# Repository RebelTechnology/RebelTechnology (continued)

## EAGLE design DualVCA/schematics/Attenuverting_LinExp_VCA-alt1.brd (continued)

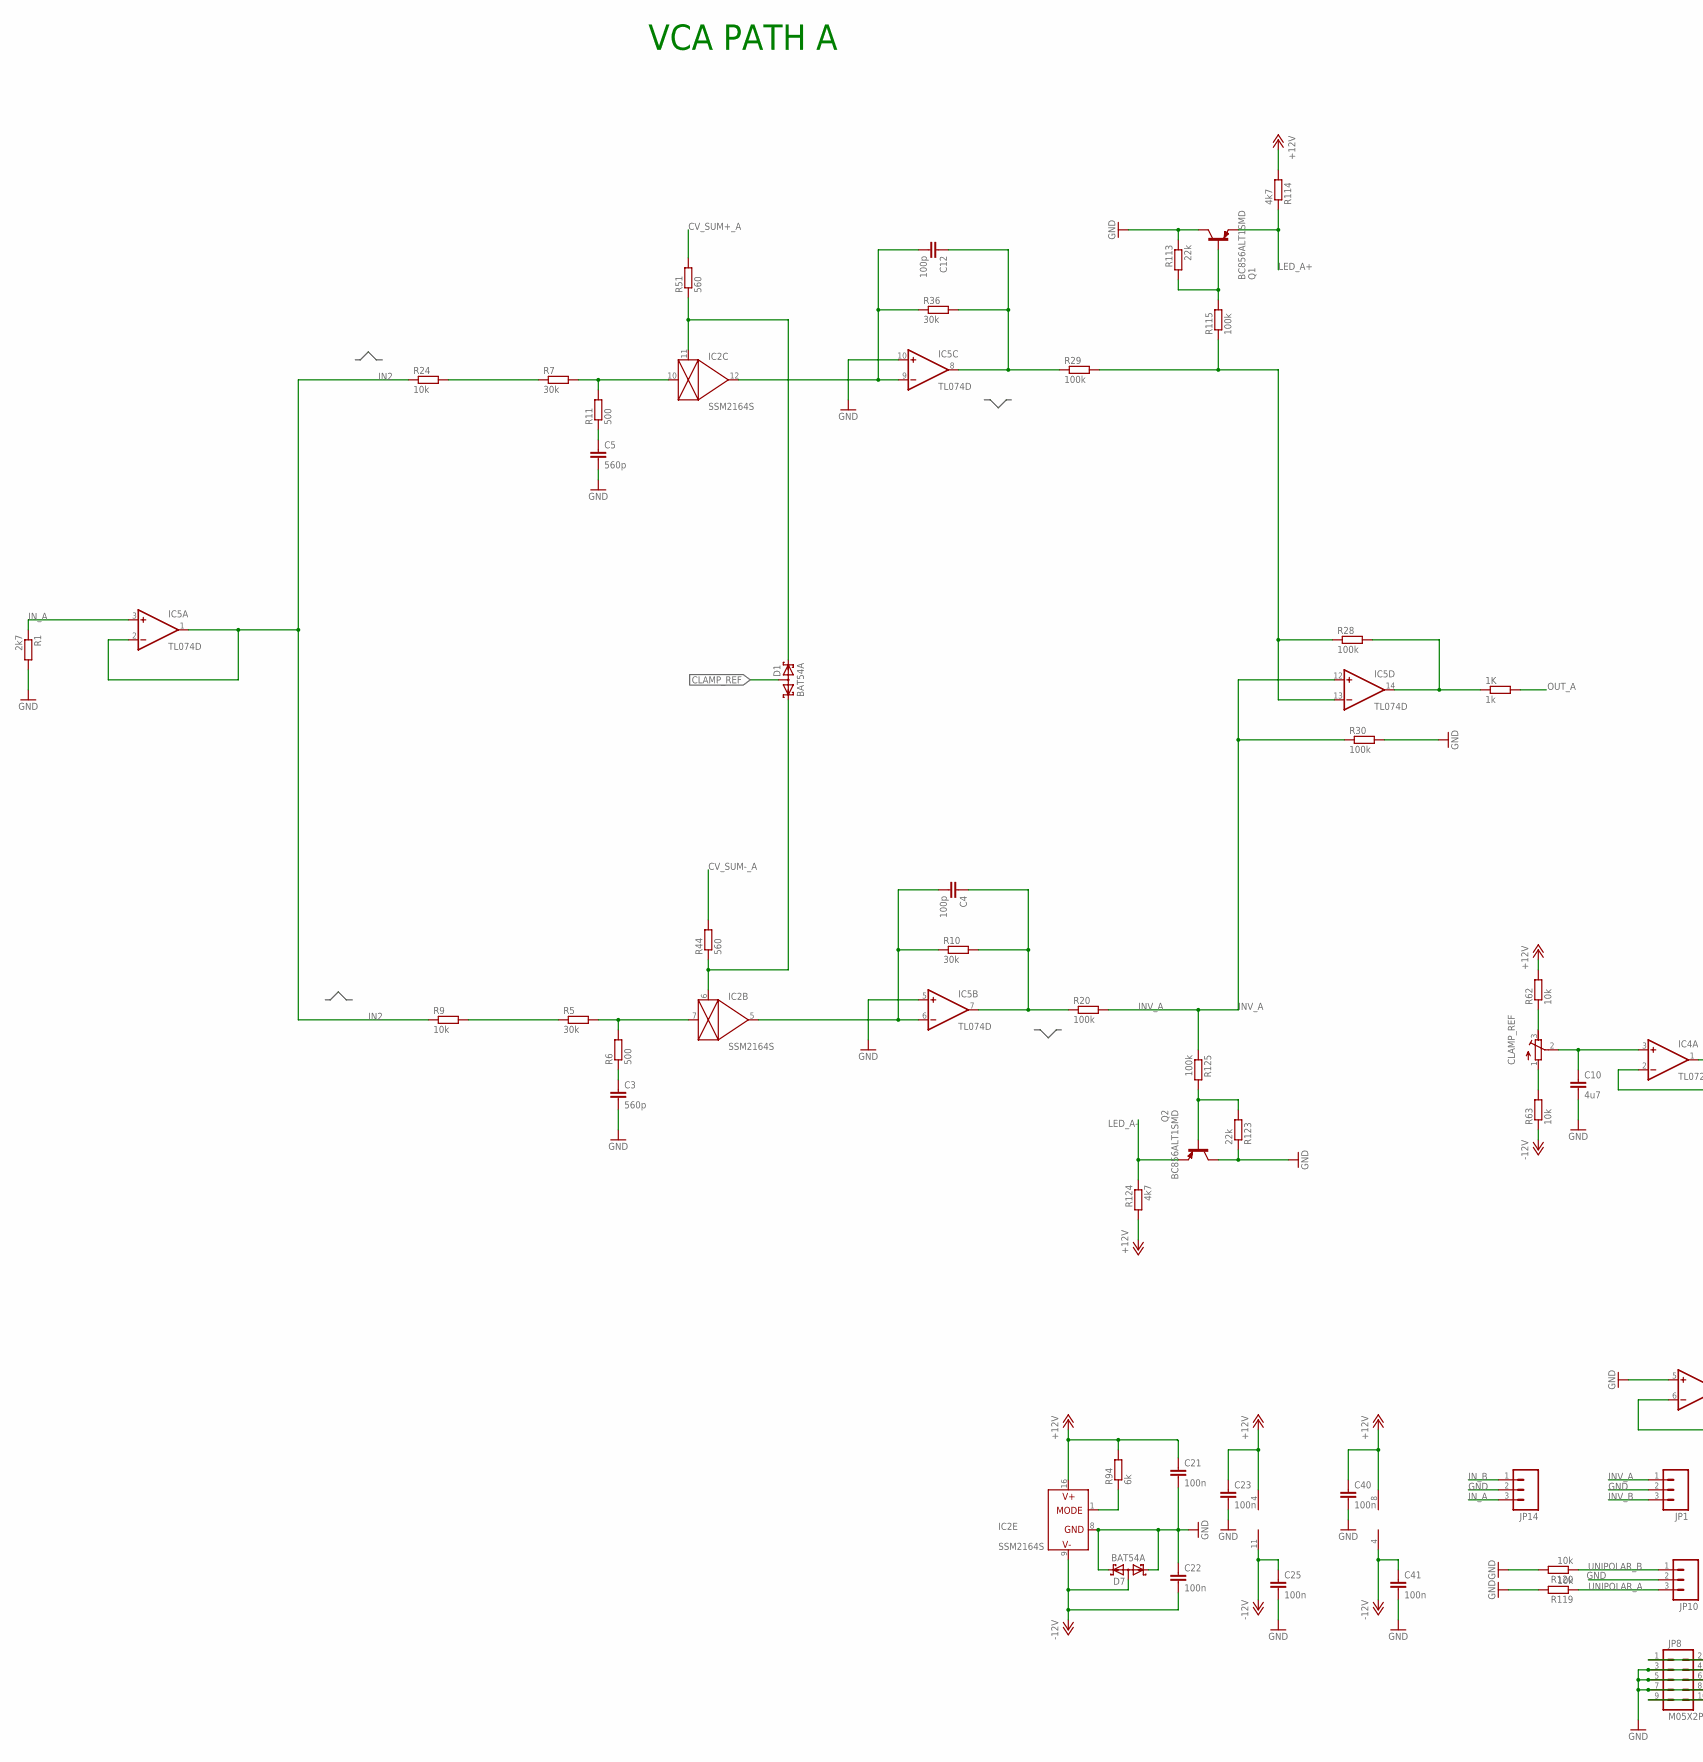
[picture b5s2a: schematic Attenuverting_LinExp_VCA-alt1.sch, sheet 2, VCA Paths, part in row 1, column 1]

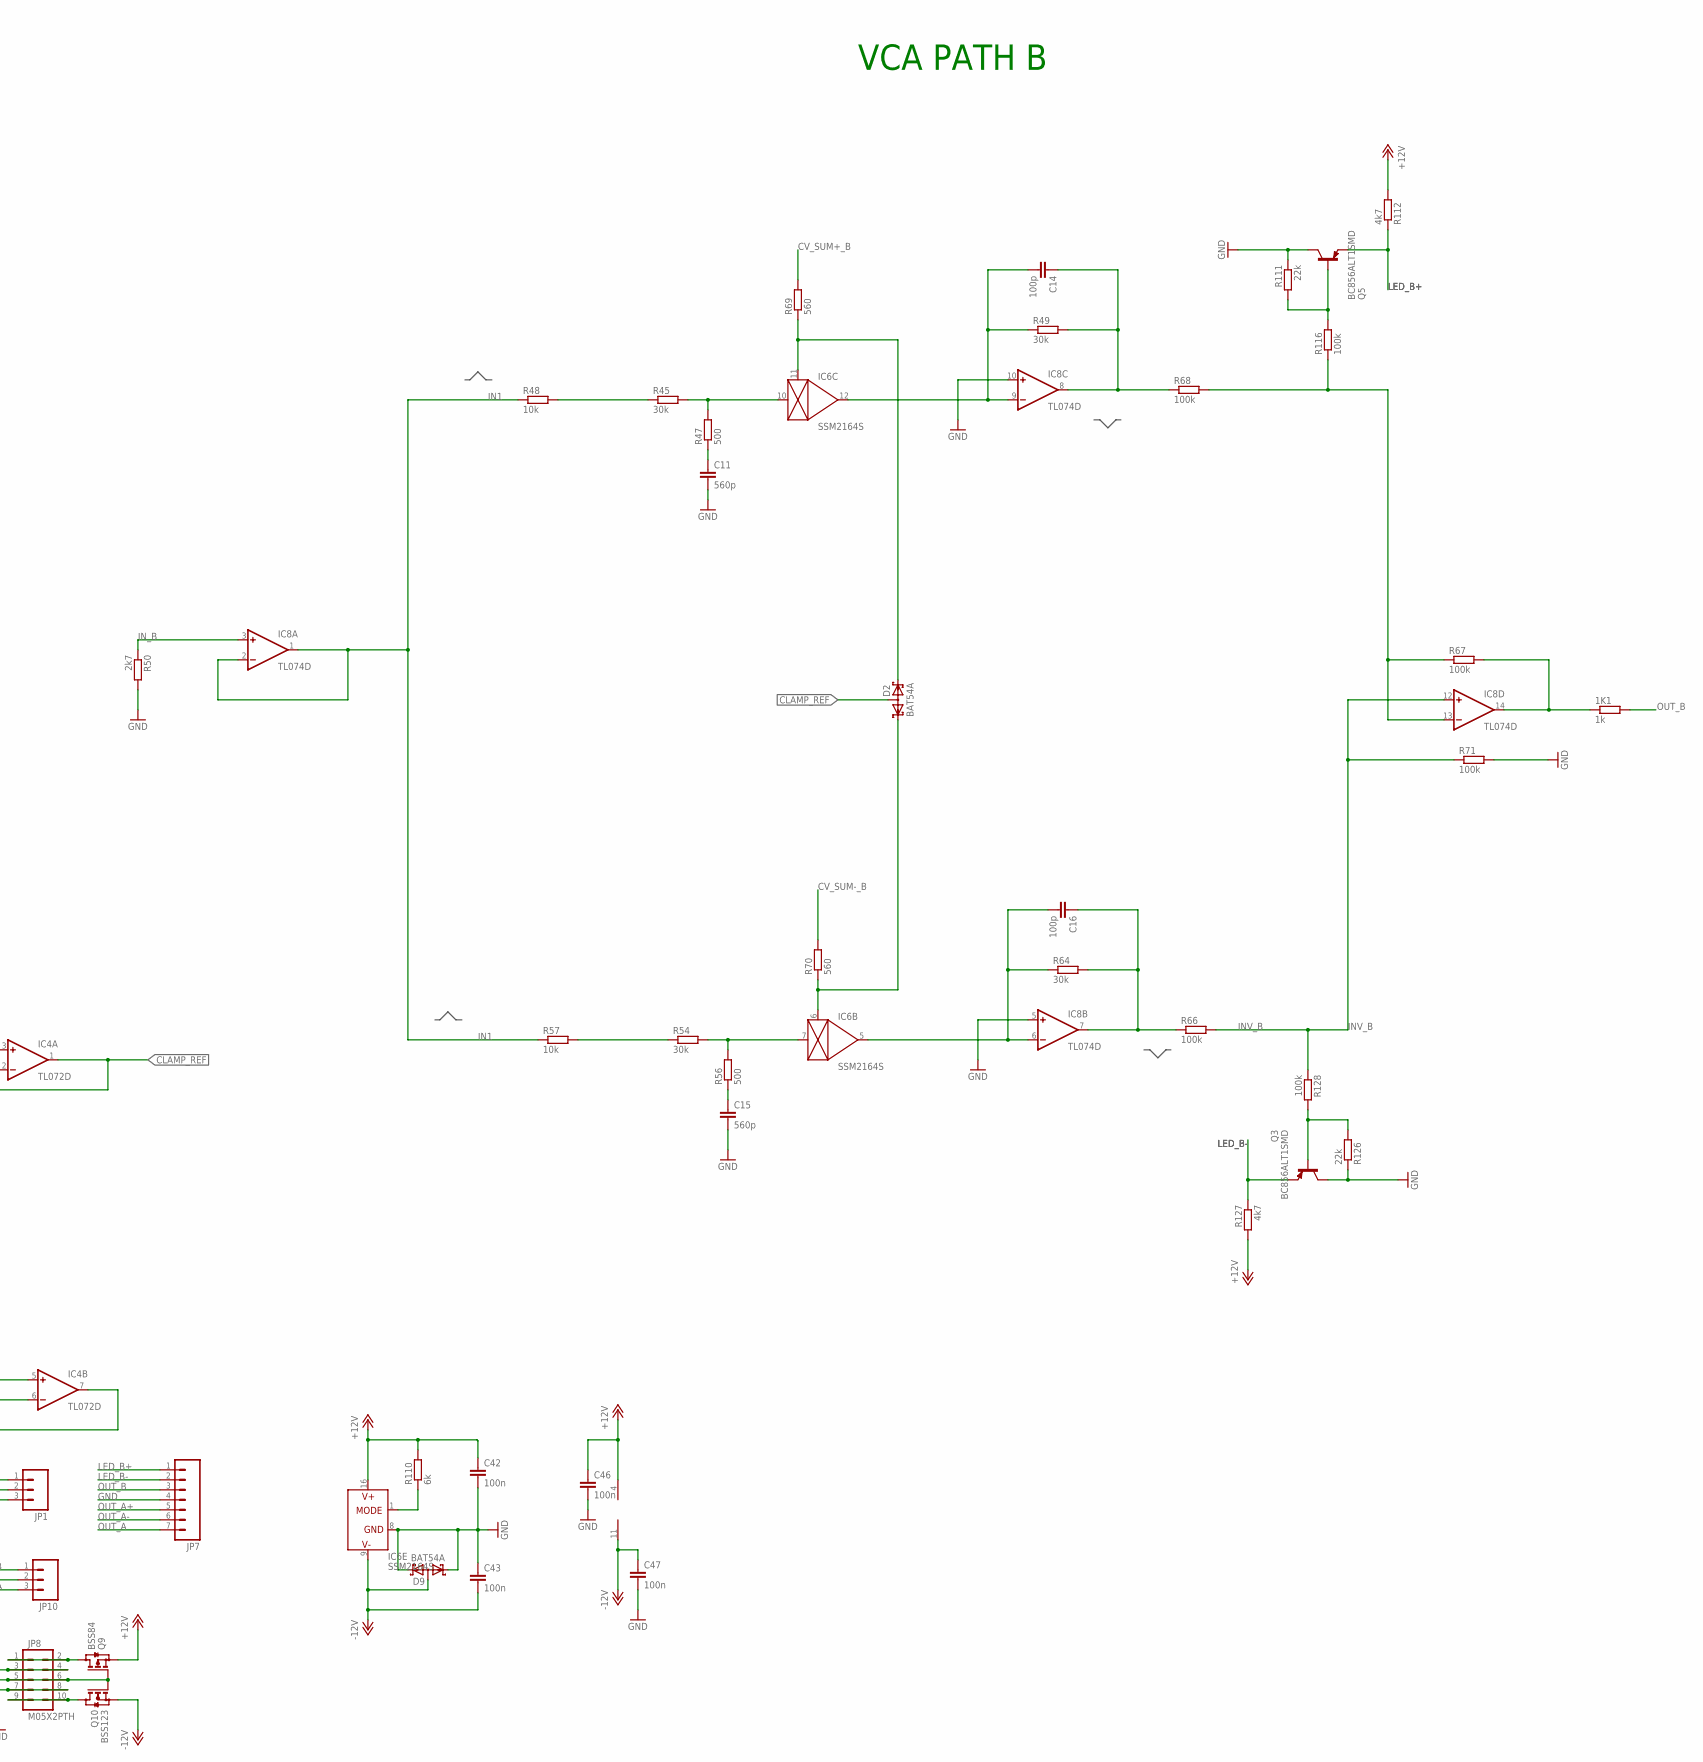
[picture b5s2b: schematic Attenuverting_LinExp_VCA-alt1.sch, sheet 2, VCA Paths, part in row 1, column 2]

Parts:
1K, 1K1: 1k; 0603; MPN MC0063W06031160K
C3, C5, C11, C15: 560p; C0603K
C4, C12, C14, C16: 100p; C0603K
C10: 4u7; C0603K
C21, C22, C23, C25, C40, C41, C42, C43, C46, C47: 100n; C0603K
CLAMP_REF: R-TRIMM64W; RTRIM64W
D1, D2, D7, D9: BAT54A; SOT23
IC2, IC6: SSM2164S; SOIC16N
IC4: TL072D; SO08
IC5, IC8: TL074D; SO14
JP1, JP10, JP14: M03PTH; 1X03
JP7: M07; 1X07
JP8: M05X2PTH; AVR_ICSP
Q1, Q2, Q3, Q5: BC856ALT1SMD; SOT23-BEC
Q9: BSS84; SOT23
Q10: BSS123; SOT23
R1, R50: 2k7; 0603
R5, R7, R10, R36, R45, R49, R54, R64: 30k; 0603
R6, R11, R47, R56: 500; 0603
R9, R24, R48, R57, R62, R63, R119, R120: 10k; 0603
R20, R28, R29, R30, R66, R67, R68, R71, R115, R116, R125, R128: 100k; 0603
R44, R51, R69, R70: 560; 0603
R94, R110: 6k; 0603
R111, R113, R123, R126: 22k; 0603
R112, R114, R124, R127: 4k7; 0603

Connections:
+12V: C21.1, C23.1, C40.1, C42.1, C46.1, IC2.16 (V+), IC4.8 (V+), IC5.4 (V+), IC6.16 (V+), IC8.4 (V+), Q9.2 (S), R62.2, R94.2, R110.2, R112.2, R114.2, R124.2, R127.2; also elsewhere on the board
-12V: C22.2, C25.1, C41.1, C43.2, C47.1, D7.3 (AA), D9.3 (AA), IC2.9 (V-), IC4.4 (V-), IC5.11 (V-), IC6.9 (V-), IC8.11 (V-), Q10.2 (S), R63.1; also elsewhere on the board
CLAMP_REF: D1.3 (AA), D2.3 (AA), IC4.1 (OUT), IC4.2 (-IN)
CV_SUM+_A: R51.2; also elsewhere on the board
CV_SUM+_B: R69.2; also elsewhere on the board
CV_SUM-_A: R44.2; also elsewhere on the board
CV_SUM-_B: R70.2; also elsewhere on the board
GND: C3.2, C5.2, C10.2, C11.2, C15.2, C21.2, C22.1, C23.2, C25.2, C40.2, C41.2, C42.2, C43.1, C46.2, C47.2, D7.1 (K1), D7.2 (K2), D9.1 (K1), D9.2 (K2), IC2.8 (GND), IC4.5 (+IN), IC5.5 (+IN), IC5.10 (+IN), IC6.8 (GND), IC8.5 (+IN), IC8.10 (+IN), JP1.2, JP7.4, JP8.3, JP8.4, JP8.5, JP8.6, JP8.7, JP8.8, JP10.2, JP14.2, Q1.C, Q2.C, Q3.C, Q5.C, Q9.1 (G), Q10.1 (G), R1.2, R30.2, R50.2, R71.2, R111.1, R113.1, R119.2, R120.2, R123.1, R126.1; also elsewhere on the board
IC2B_1: D2.1 (K1), IC6.6 (CTRL), R70.1
IC2B_6: D1.1 (K1), IC2.6 (CTRL), R44.1
IC2C_1: D2.2 (K2), IC6.11 (CTRL), R69.1
IC2C_11: D1.2 (K2), IC2.11 (CTRL), R51.1
IN1: IC8.1 (OUT), IC8.2 (-IN), R48.1, R57.1
IN2: IC5.1 (OUT), IC5.2 (-IN), R9.1, R24.1
INV_A: IC5.12 (+IN), JP1.1, R20.2, R30.1, R125.1; also elsewhere on the board
INV_B: IC8.12 (+IN), JP1.3, R66.2, R71.1, R128.1; also elsewhere on the board
IN_A: IC5.3 (+IN), JP14.3, R1.1; also elsewhere on the board
IN_B: IC8.3 (+IN), JP14.1, R50.1; also elsewhere on the board
LED_A+: Q1.E, R114.1; also elsewhere on the board
LED_A-: Q2.E, R124.1; also elsewhere on the board
LED_B+: JP7.1, Q5.E, R112.1; also elsewhere on the board
LED_B-: JP7.2, Q3.E, R127.1; also elsewhere on the board
unnamed: JP8.9, JP8.10, Q10.3 (D)
unnamed: C3.1, R6.1
unnamed: JP8.1, JP8.2, Q9.3 (D)
unnamed: Q2.B, R123.2, R125.2
unnamed: IC5.13 (-IN), R28.1, R29.2, R115.1
unnamed: IC2.7 (IN), R5.2, R6.2
unnamed: R5.1, R9.2
unnamed: C5.1, R11.1
unnamed: C4.2, IC2.5 (OUT), IC5.6 (-IN), R10.1
unnamed: C4.1, IC5.7 (OUT), R10.2, R20.1
unnamed: IC2.10 (IN), R7.2, R11.2
unnamed: 1K.1, IC5.14 (OUT), R28.2
unnamed: C11.1, R47.1
unnamed: R7.1, R24.2
unnamed: Q3.B, R126.2, R128.2
unnamed: IC6.10 (IN), R45.2, R47.2
unnamed: CLAMP_REF.3 (E), R62.1
unnamed: Q5.B, R111.2, R116.2
unnamed: R45.1, R48.2
unnamed: C14.2, IC6.12 (OUT), IC8.9 (-IN), R49.1
unnamed: C14.1, IC8.8 (OUT), R49.2, R68.1
unnamed: C15.1, R56.1
unnamed: IC6.7 (IN), R54.2, R56.2
unnamed: C12.2, IC2.12 (OUT), IC5.9 (-IN), R36.1
unnamed: R54.1, R57.2
unnamed: C12.1, IC5.8 (OUT), R29.1, R36.2
unnamed: C16.2, IC6.5 (OUT), IC8.6 (-IN), R64.1
unnamed: CLAMP_REF.1 (A), R63.2
unnamed: C10.1, CLAMP_REF.2 (S), IC4.3 (+IN)
unnamed: C16.1, IC8.7 (OUT), R64.2, R66.1
unnamed: IC8.13 (-IN), R67.1, R68.2, R116.1
unnamed: 1K1.1, IC8.14 (OUT), R67.2
unnamed: IC2.1 (MODE), R94.1
unnamed: IC4.6 (-IN), IC4.7 (OUT)
unnamed: Q1.B, R113.2, R115.2
unnamed: IC6.1 (MODE), R110.1
OUT_A: 1K.2, JP7.7; also elsewhere on the board
OUT_A+: JP7.5
OUT_A-: JP7.6
OUT_B: 1K1.2, JP7.3; also elsewhere on the board
UNIPOLAR_A: JP10.3, R119.1; also elsewhere on the board
UNIPOLAR_B: JP10.1, R120.1; also elsewhere on the board

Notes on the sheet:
VCA PATH A
VCA PATH B

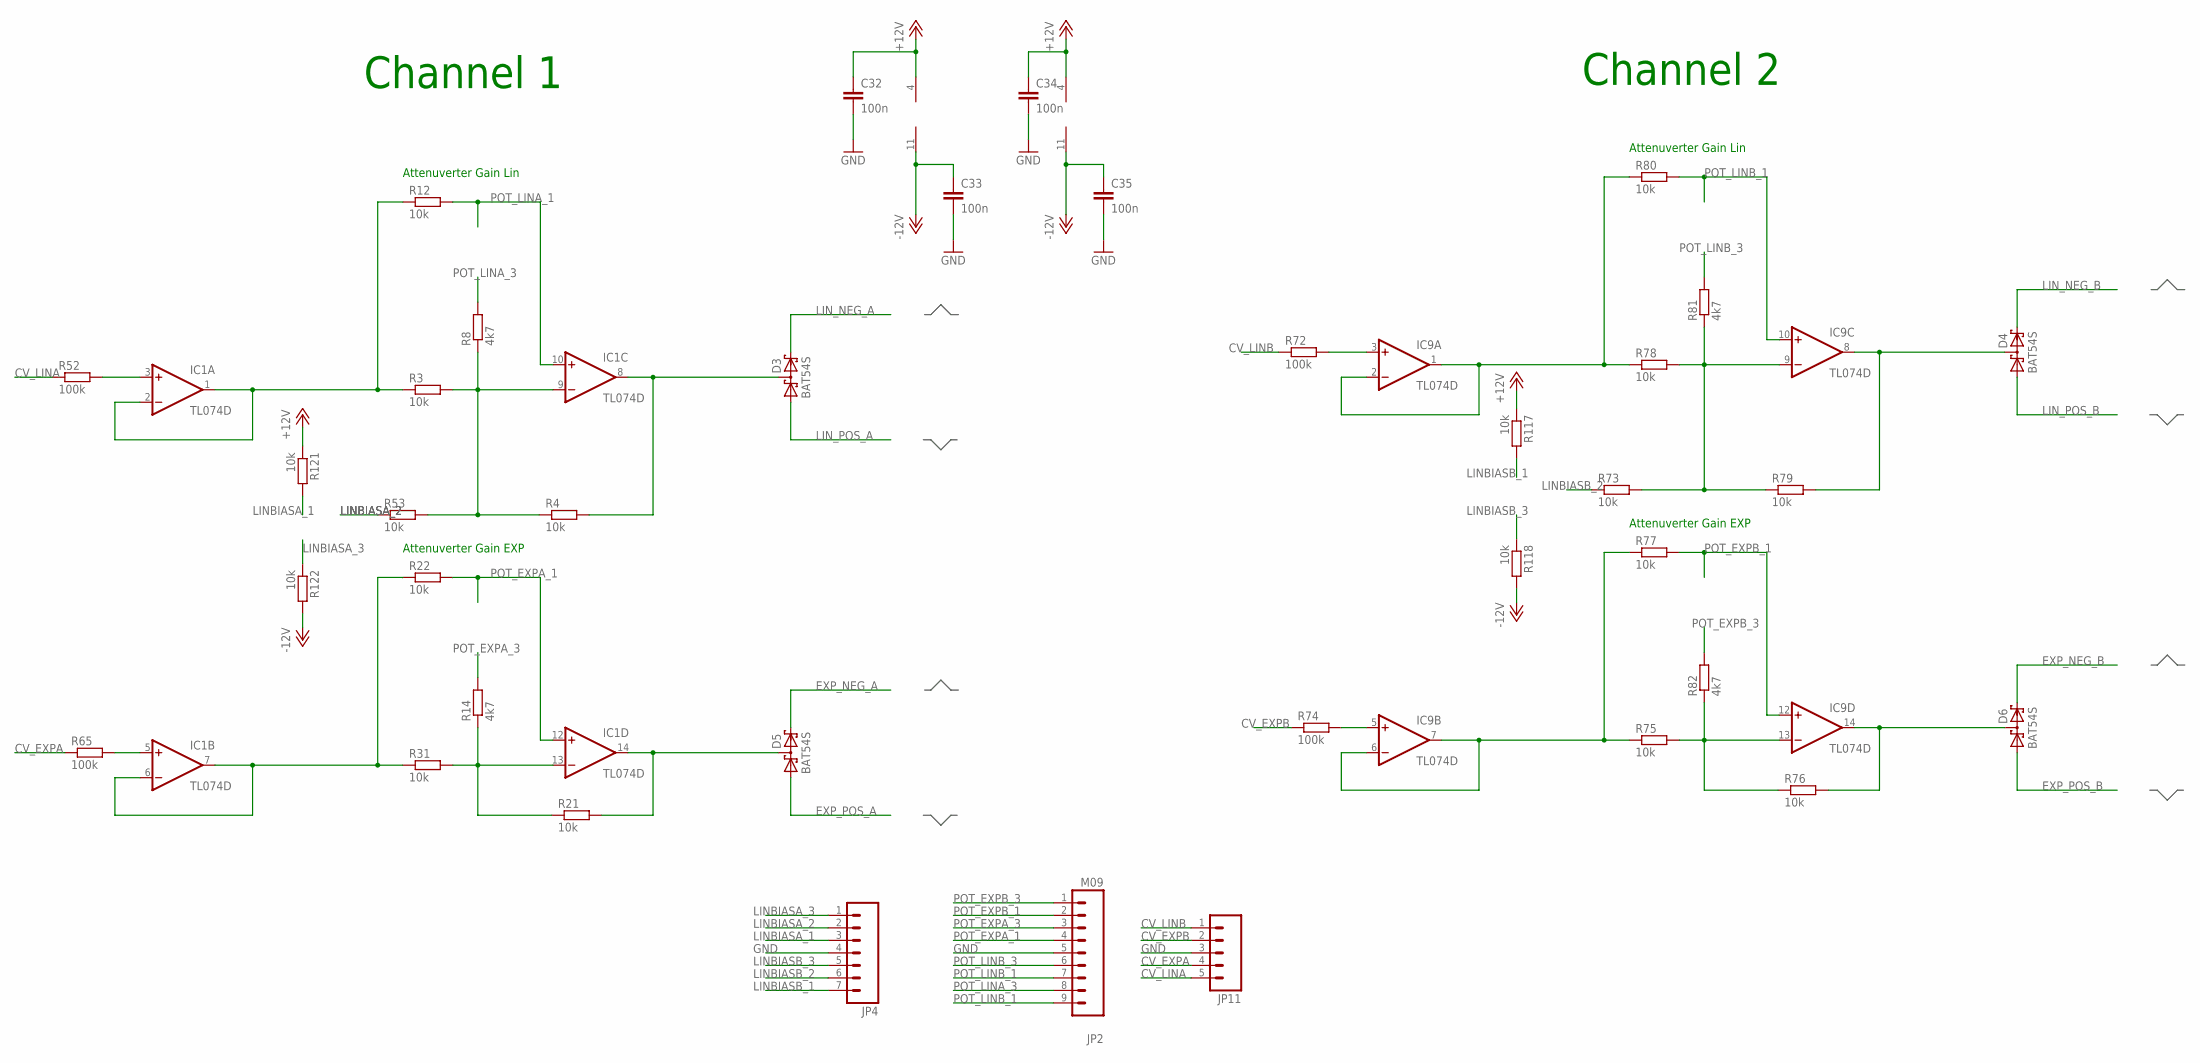
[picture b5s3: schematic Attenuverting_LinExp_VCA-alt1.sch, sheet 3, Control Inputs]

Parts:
C32, C33, C34, C35: 100n; C0603K
D3, D4, D5, D6: BAT54S; SOT23
IC1, IC9: TL074D; SO14
JP2: M09; 1X09
JP4: M07; 1X07
JP11: M05PTH; 1X05
R3, R4, R12, R21, R22, R31, R53, R73, R75, R76, R77, R78, R79, R80, R117, R118, R121, R122: 10k; 0603
R8, R14, R81, R82: 4k7; 0603
R52, R65, R72, R74: 100k; 0603

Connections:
+12V: C32.1, C34.1, IC1.4 (V+), IC9.4 (V+), R117.1, R121.1; also elsewhere on the board
-12V: C33.1, C35.1, IC1.11 (V-), IC9.11 (V-), R118.2, R122.2; also elsewhere on the board
CV_1+: IC1.6 (-IN), IC1.7 (OUT), R22.1, R31.1
CV_1+1: IC9.6 (-IN), IC9.7 (OUT), R75.1, R77.1
CV_1-: IC1.1 (OUT), IC1.2 (-IN), R3.1, R12.1
CV_1-1: IC9.1 (OUT), IC9.2 (-IN), R78.1, R80.1
CV_EXPA: JP11.4, R65.1; also elsewhere on the board
CV_EXPB: JP11.2, R74.1; also elsewhere on the board
CV_LINA: JP11.5, R52.1; also elsewhere on the board
CV_LINB: JP11.1, R72.1; also elsewhere on the board
EXP_NEG_A: D5.2 (C2); also elsewhere on the board
EXP_NEG_B: D6.2 (C2); also elsewhere on the board
EXP_POS_A: D5.1 (A1); also elsewhere on the board
EXP_POS_B: D6.1 (A1); also elsewhere on the board
GND: C32.2, C33.2, C34.2, C35.2, JP2.5, JP4.4, JP11.3; also elsewhere on the board
LINBIASA_1: JP4.3, R121.2; also elsewhere on the board
LINBIASA_2: JP4.2, R53.1; also elsewhere on the board
LINBIASA_3: JP4.1, R122.1; also elsewhere on the board
LINBIASB_1: JP4.7, R117.2; also elsewhere on the board
LINBIASB_2: JP4.6, R73.1; also elsewhere on the board
LINBIASB_3: JP4.5, R118.1; also elsewhere on the board
LIN_NEG_A: D3.2 (C2); also elsewhere on the board
LIN_NEG_B: D4.2 (C2); also elsewhere on the board
LIN_POS_A: D3.1 (A1); also elsewhere on the board
LIN_POS_B: D4.1 (A1); also elsewhere on the board
unnamed: D3.3 (C1A2), IC1.8 (OUT), R4.2
unnamed: IC1.3 (+IN), R52.2
unnamed: IC1.5 (+IN), R65.2
unnamed: IC1.13 (-IN), R14.1, R21.1, R31.2
unnamed: IC1.9 (-IN), R3.2, R4.1, R8.1, R53.2
unnamed: D6.3 (C1A2), IC9.14 (OUT), R76.2
unnamed: IC9.13 (-IN), R75.2, R76.1, R82.1
unnamed: D4.3 (C1A2), IC9.8 (OUT), R79.2
unnamed: IC9.3 (+IN), R72.2
unnamed: IC9.5 (+IN), R74.2
unnamed: IC9.9 (-IN), R73.2, R78.2, R79.1, R81.1
unnamed: D5.3 (C1A2), IC1.14 (OUT), R21.2
POT_EXPA_1: IC1.12 (+IN), JP2.4, R22.2; also elsewhere on the board
POT_EXPA_3: JP2.3, R14.2; also elsewhere on the board
POT_EXPB_1: IC9.12 (+IN), JP2.2, R77.2; also elsewhere on the board
POT_EXPB_3: JP2.1, R82.2; also elsewhere on the board
POT_LINA_1: IC1.10 (+IN), R12.2; also elsewhere on the board
POT_LINA_3: JP2.8, R8.2; also elsewhere on the board
POT_LINB_1: IC9.10 (+IN), JP2.7, JP2.9, R80.2; also elsewhere on the board
POT_LINB_3: JP2.6, R81.2; also elsewhere on the board

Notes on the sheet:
Attenuverter Gain Lin
Attenuverter Gain EXP
Channel 1
Channel 2

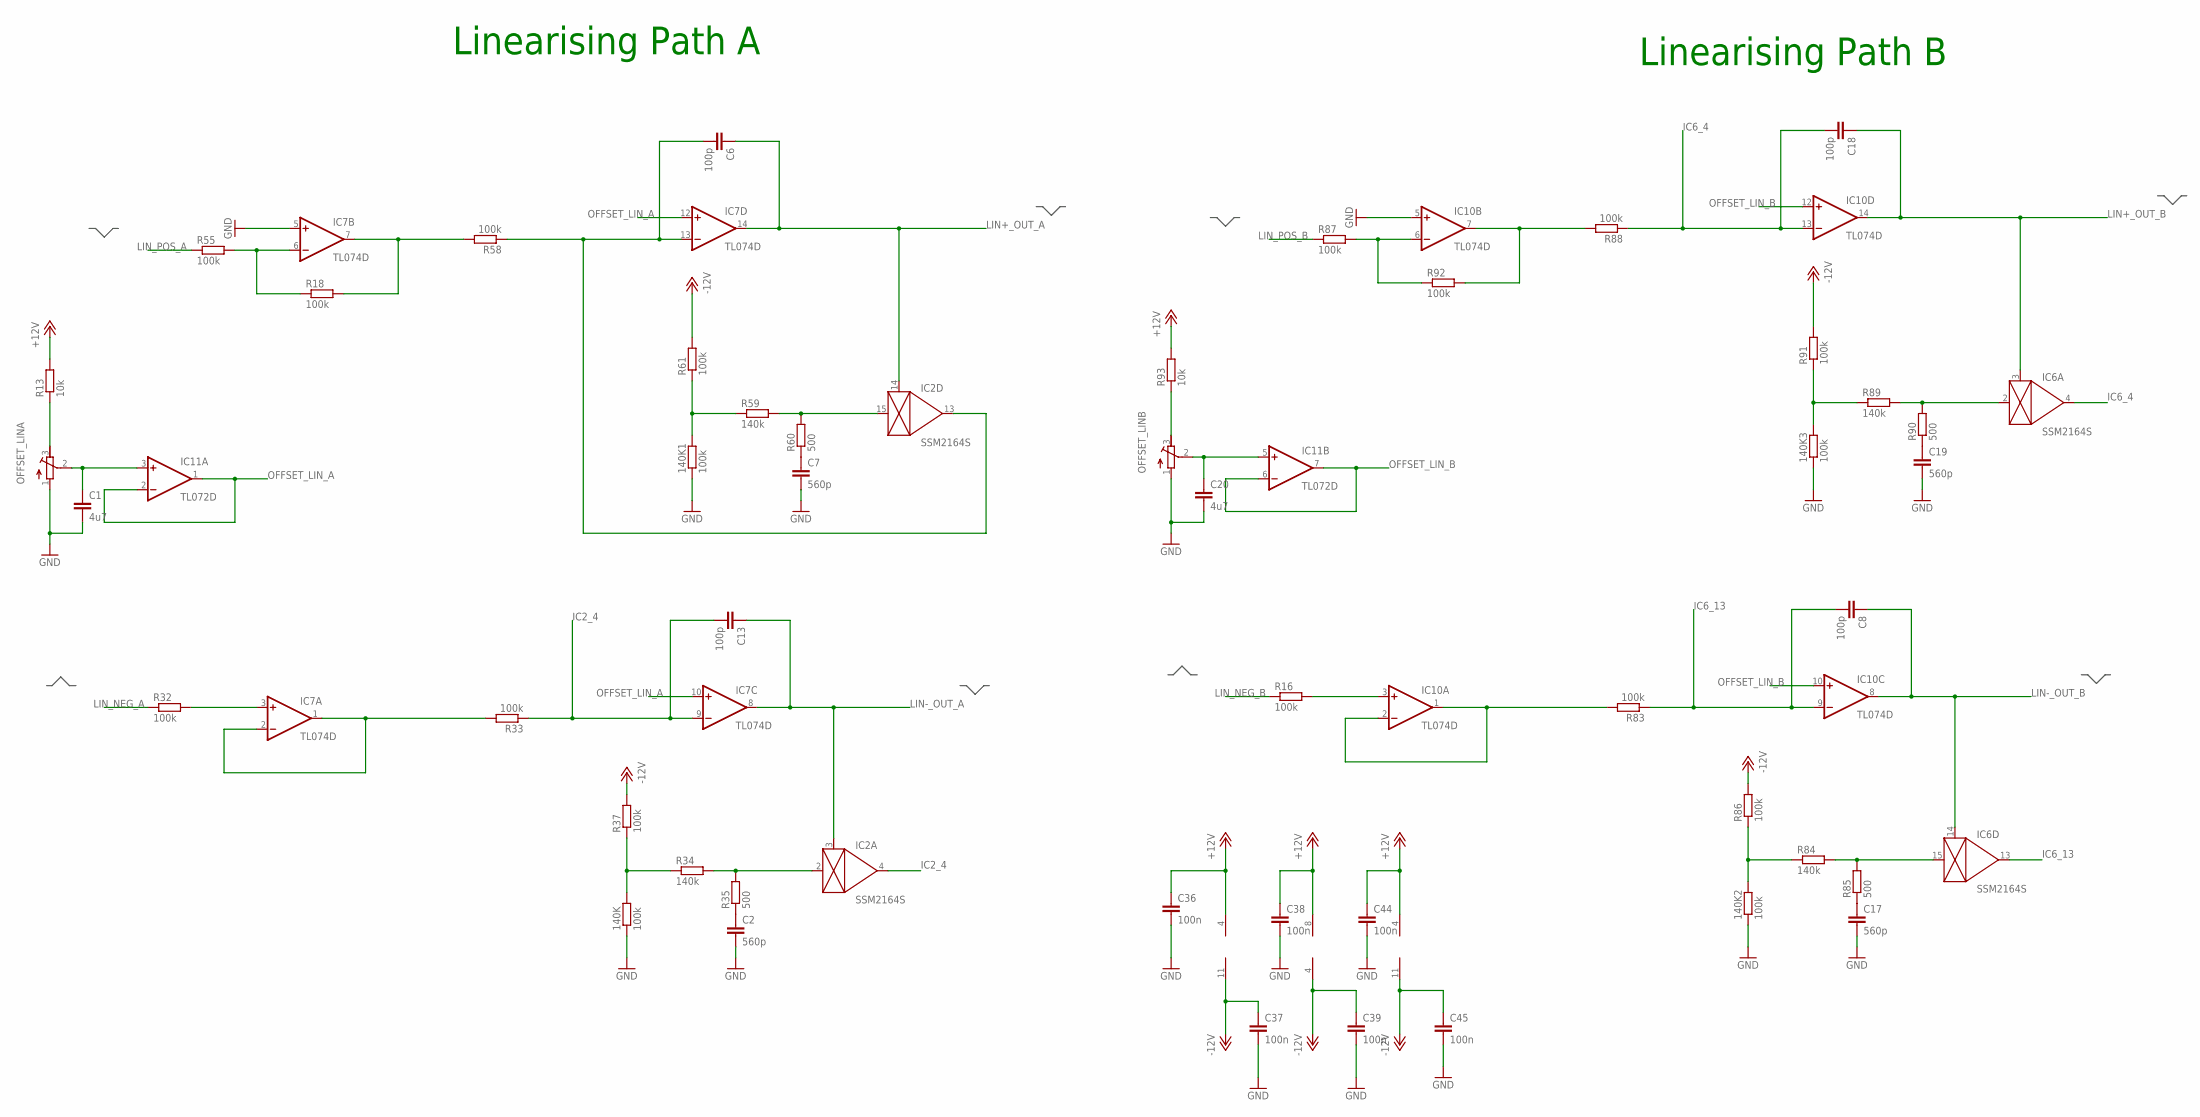
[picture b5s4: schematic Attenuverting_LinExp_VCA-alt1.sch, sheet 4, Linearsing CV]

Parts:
140K, 140K1, 140K2, 140K3: 100k; 0603
C1, C20: 4u7; C0603K
C2, C7, C17, C19: 560p; C0603K
C6, C8, C13, C18: 100p; C0603K
C36, C37, C38, C39, C44, C45: 100n; C0603K
IC2, IC6: SSM2164S; SOIC16N
IC7, IC10: TL074D; SO14
IC11: TL072D; SO08
OFFSET_LINA: R-TRIMM64W; RTRIM64W
OFFSET_LINB: R-TRIMM64W; RTRIM64W
R13, R93: 10k; 0603
R16, R18, R32, R33, R37, R55, R58, R61, R83, R86, R87, R88, R91, R92: 100k; 0603
R34, R59, R84, R89: 140k; 0603
R35, R60, R85, R90: 500; 0603

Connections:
+12V: C36.1, C38.1, C44.1, IC7.4 (V+), IC10.4 (V+), IC11.8 (V+), R13.2, R93.2; also elsewhere on the board
-10V: 140K.2, R34.1, R37.1
-10V1: 140K1.2, R59.1, R61.1
-10V2: 140K3.2, R89.1, R91.1
-10V3: 140K2.2, R84.1, R86.1
-12V: C37.1, C39.1, C45.1, IC7.11 (V-), IC10.11 (V-), IC11.4 (V-), R37.2, R61.2, R86.2, R91.2; also elsewhere on the board
GND: 140K.1, 140K1.1, 140K2.1, 140K3.1, C1.2, C2.2, C7.2, C17.2, C19.2, C20.2, C36.2, C37.2, C38.2, C39.2, C44.2, C45.2, IC7.5 (+IN), IC10.5 (+IN), OFFSET_LINA.1 (A), OFFSET_LINB.1 (A); also elsewhere on the board
IC2_4: C13.2, IC2.4 (OUT), IC7.9 (-IN), R33.1
IC2_13: C6.2, IC2.13 (OUT), IC7.13 (-IN), R58.1
IC6_4: C18.2, IC6.4 (OUT), IC10.13 (-IN), R88.1
IC6_13: C8.2, IC6.13 (OUT), IC10.9 (-IN), R83.1
LIN+_OUT_A: C6.1, IC2.14 (CTRL), IC7.14 (OUT); also elsewhere on the board
LIN+_OUT_B: C18.1, IC6.3 (CTRL), IC10.14 (OUT); also elsewhere on the board
LIN-_OUT_A: C13.1, IC2.3 (CTRL), IC7.8 (OUT); also elsewhere on the board
LIN-_OUT_B: C8.1, IC6.14 (CTRL), IC10.8 (OUT); also elsewhere on the board
LIN_NEG_A: R32.1; also elsewhere on the board
LIN_NEG_B: R16.1; also elsewhere on the board
LIN_POS_A: R55.1; also elsewhere on the board
LIN_POS_B: R87.1; also elsewhere on the board
unnamed: IC7.1 (OUT), IC7.2 (-IN), R33.2
unnamed: C2.1, R35.1
unnamed: IC2.2 (IN), R34.2, R35.2
unnamed: IC7.6 (-IN), R18.1, R55.2
unnamed: IC10.7 (OUT), R88.2, R92.2
unnamed: C19.1, R90.1
unnamed: OFFSET_LINA.3 (E), R13.1
unnamed: C1.1, IC11.3 (+IN), OFFSET_LINA.2 (S)
unnamed: IC7.3 (+IN), R32.2
unnamed: IC7.7 (OUT), R18.2, R58.2
unnamed: C7.1, R60.1
unnamed: IC2.15 (IN), R59.2, R60.2
unnamed: IC6.2 (IN), R89.2, R90.2
unnamed: IC10.1 (OUT), IC10.2 (-IN), R83.2
unnamed: IC10.3 (+IN), R16.2
unnamed: C17.1, R85.1
unnamed: IC6.15 (IN), R84.2, R85.2
unnamed: IC10.6 (-IN), R87.2, R92.1
unnamed: OFFSET_LINB.3 (E), R93.1
unnamed: C20.1, IC11.5 (+IN), OFFSET_LINB.2 (S)
OFFSET_LIN_A: IC7.10 (+IN), IC7.12 (+IN), IC11.1 (OUT), IC11.2 (-IN)
OFFSET_LIN_B: IC10.10 (+IN), IC10.12 (+IN), IC11.6 (-IN), IC11.7 (OUT)

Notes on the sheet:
Linearising Path A
Linearising Path B

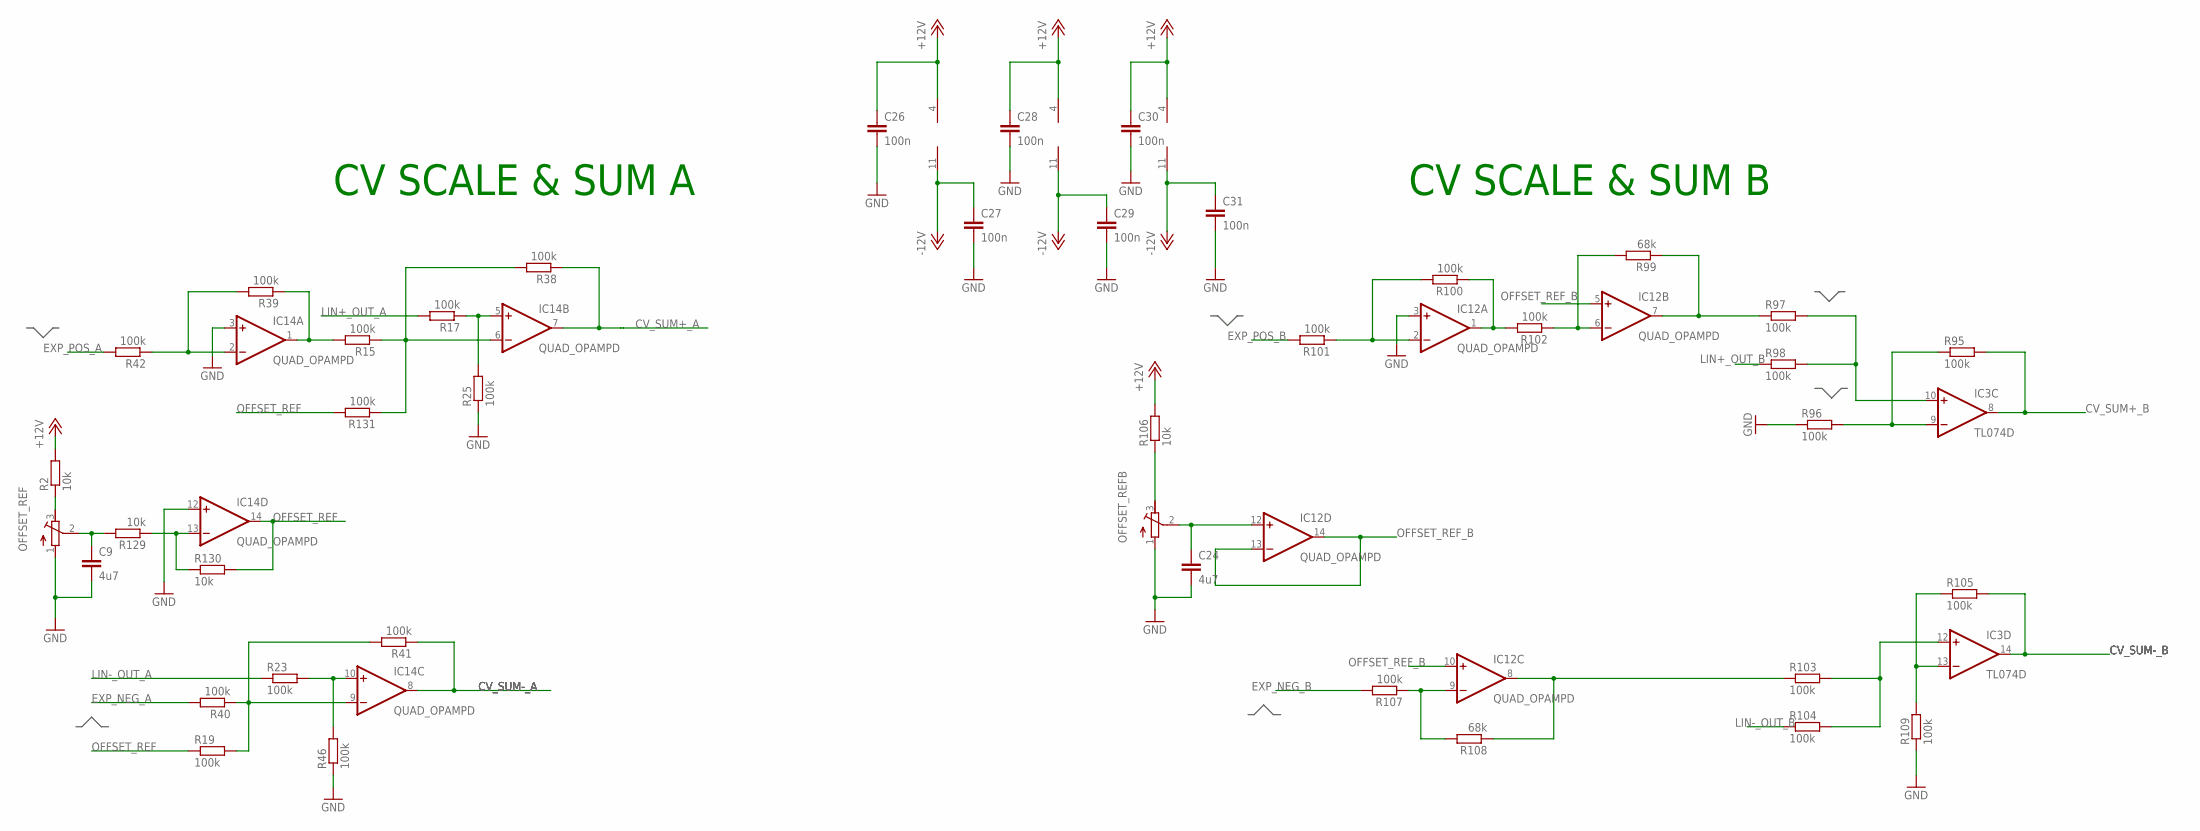
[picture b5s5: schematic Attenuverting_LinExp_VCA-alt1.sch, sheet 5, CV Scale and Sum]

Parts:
C9, C24: 4u7; C0603K
C26, C27, C28, C29, C30, C31: 100n; C0603K
IC3: TL074D; SO14
IC12, IC14: QUAD_OPAMPD; SO14
OFFSET_REF: R-TRIMM64W; RTRIM64W
OFFSET_REFB: R-TRIMM64W; RTRIM64W
R2, R106, R129, R130: 10k; 0603
R15, R17, R19, R23, R25, R38, R39, R40, R41, R42, R46, R95, R96, R97, R98, R100, R101, R102, R103, R104, R105, R107, R109, R131: 100k; 0603
R99, R108: 68k; 0603

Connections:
+12V: C26.1, C28.1, C30.1, IC3.4 (V+), IC12.4 (V+), IC14.4 (V+), R2.2, R106.2; also elsewhere on the board
-12V: C27.1, C29.1, C31.1, IC3.11 (V-), IC12.11 (V-), IC14.11 (V-); also elsewhere on the board
CV_SUM+_A: IC14.7 (OUT), R38.1; also elsewhere on the board
CV_SUM+_B: IC3.8 (OUT), R95.2; also elsewhere on the board
CV_SUM-_A: IC14.8 (OUT), R41.1; also elsewhere on the board
CV_SUM-_B: IC3.14 (OUT), R105.2; also elsewhere on the board
EXP_NEG1: IC12.8 (OUT), R103.1, R108.1
EXP_NEG_A: R40.2; also elsewhere on the board
EXP_NEG_B: R107.2; also elsewhere on the board
EXP_POS_A: R42.2; also elsewhere on the board
EXP_POS_B: R101.2; also elsewhere on the board
GND: C9.2, C24.2, C26.2, C27.2, C28.2, C29.2, C30.2, C31.2, IC12.3 (+IN), IC14.3 (+IN), IC14.12 (+IN), OFFSET_REF.1 (A), OFFSET_REFB.1 (A), R25.1, R46.1, R96.1, R109.1; also elsewhere on the board
IC2_1: IC12.7 (OUT), R97.1, R99.1
IC2_2: IC12.6 (-IN), R99.2, R102.1
IC2_8: IC14.6 (-IN), R15.1, R38.2, R131.1
LIN+_OUT_A: R17.2; also elsewhere on the board
LIN+_OUT_B: R98.1; also elsewhere on the board
LIN-_OUT_A: R23.1; also elsewhere on the board
LIN-_OUT_B: R104.1; also elsewhere on the board
unnamed: IC14.10 (+IN), R23.2, R46.2
unnamed: IC14.5 (+IN), R17.1, R25.2
unnamed: IC14.1 (OUT), R15.2, R39.1
unnamed: IC14.2 (-IN), R39.2, R42.1
unnamed: OFFSET_REF.3 (E), R2.1
unnamed: C9.1, OFFSET_REF.2 (S), R129.2
unnamed: IC14.9 (-IN), R19.2, R40.1, R41.2
unnamed: IC14.13 (-IN), R129.1, R130.1
unnamed: IC3.10 (+IN), R97.2, R98.2
unnamed: IC3.9 (-IN), R95.1, R96.2
unnamed: IC12.2 (-IN), R100.2, R101.1
unnamed: IC12.1 (OUT), R100.1, R102.2
unnamed: IC3.12 (+IN), R103.2, R104.2
unnamed: OFFSET_REFB.3 (E), R106.1
unnamed: C24.1, IC12.12 (+IN), OFFSET_REFB.2 (S)
unnamed: IC12.9 (-IN), R107.1, R108.2
unnamed: IC3.13 (-IN), R105.1, R109.2
OFFSET_REF: IC14.14 (OUT), R19.1, R130.2, R131.2
OFFSET_REF_B: IC12.5 (+IN), IC12.10 (+IN), IC12.13 (-IN), IC12.14 (OUT)

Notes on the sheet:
CV SCALE & SUM A
CV SCALE & SUM B

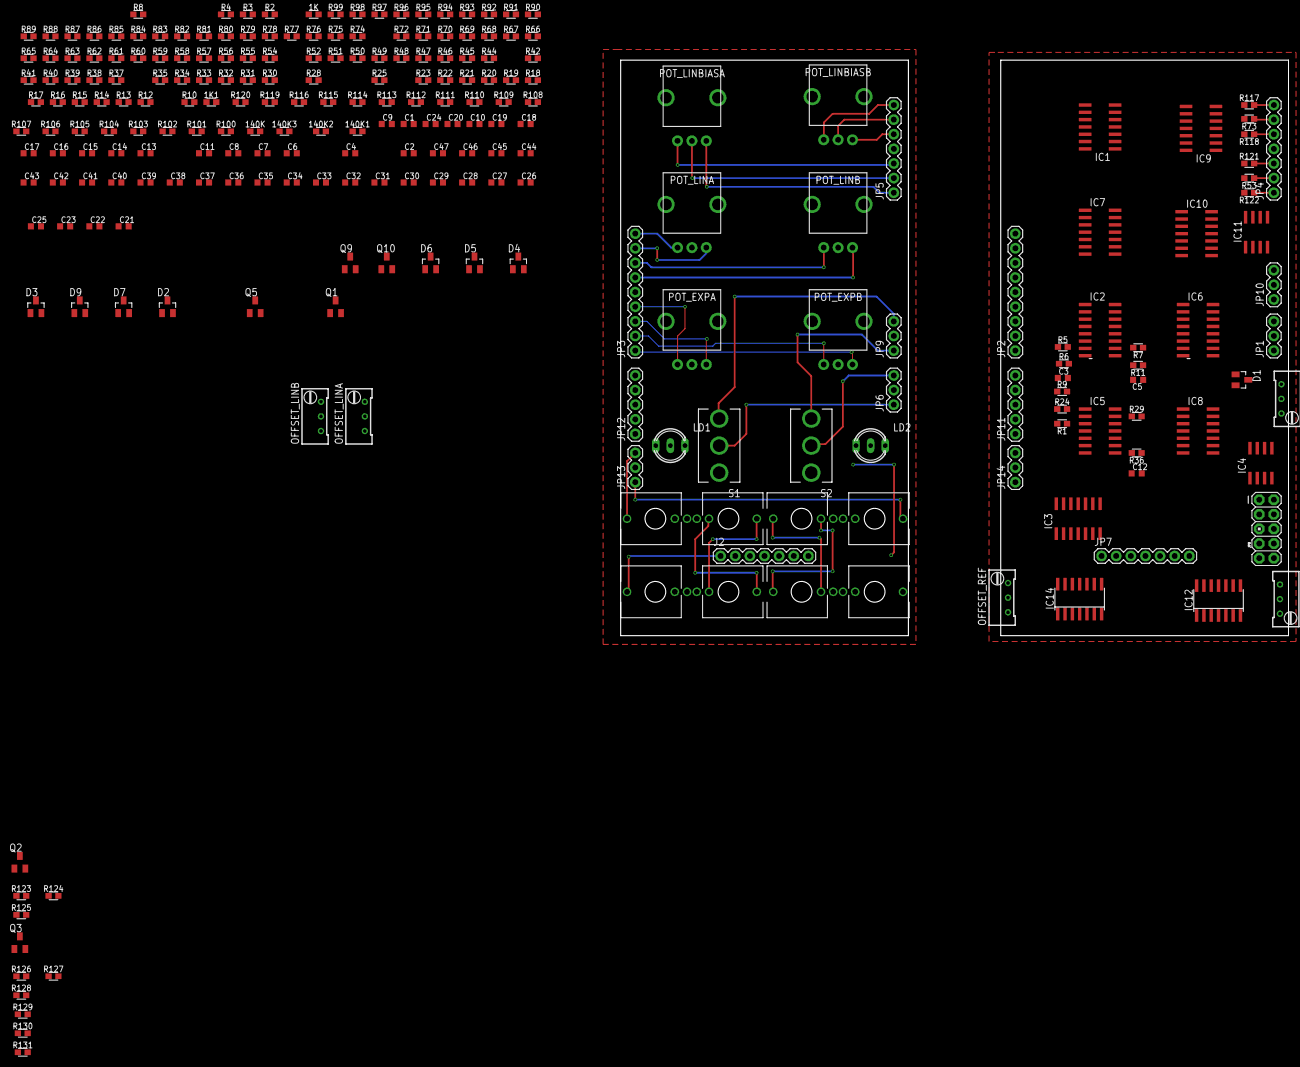
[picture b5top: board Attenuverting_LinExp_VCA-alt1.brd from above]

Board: 2 copper layers, 116.0 x 100.0 mm, 246 parts (0 on the bottom side), 161 nets.
